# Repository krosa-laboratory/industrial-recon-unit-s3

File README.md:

# Tactical Cyber-Recon Architecture (Edge-to-C2)

A distributed, Wireless Intrusion Detection System (WIDS) and Signal Intelligence (SIGINT) platform. 

This project separates data acquisition from analysis. It utilizes an ESP32-S3 as a headless, RF edge sensor that streams raw 802.11 and BLE frames via high-speed telemetry to a Python-based Command & Control station for real-time processing, OSINT enrichment, and visualization.

## The Edge Node (Headless ESP32-S3)
A bare-metal, RTOS-driven sensor optimized for maximum radio duty-cycle and zero GUI overhead.

* **MCU:** ESP32-S3-WROOM-1 (Dual-Core Xtensa LX7)
* **Firmware:** PlatformIO / FreeRTOS (C++)
* **Architecture:**
  * **Core 0 (RF Engine):** Dedicated to hardware-level interrupts, 802.11 Promiscuous mode, CSI (Channel State Information) extraction, and passive BLE scanning.
  * **Core 1 (Telemetry Link):** Dedicated to consuming RTOS queues, serializing data into lightweight JSON, and streaming via UART at 921600 baud without blocking the radio.

## The Command & Control Station (Python GUI)
A desktop application for data ingestion, decoding, and tactical analysis.

* **Tech Stack:** Python 3, PyQt6 (UI/UX), PyQtGraph (Real-time data viz), PySerial (Async ingestion).
* **Key Capabilities:**
  * **OSINT Tracker:** Cross-references captured MAC addresses with local OUI databases to identify device manufacturers and track historical Wi-Fi probe requests.
  * **WIDS Dashboard:** Real-time detection of Deauthentication bursts, Rogue APs, and BLE saturation attacks.
  * **CSI Radar:** Generates live waterfall plots from 802.11 subcarrier perturbations to detect physical presence via microwave reflections.
  * **BLE Ecosystem Sniffer:** Parses raw Bluetooth Low Energy payloads to track corporate/IoT devices and exposes unencrypted GATT profiles.

## 🛠️ Development Philosophy & Post-Mortem
*Note: This architecture is a evolution from an initial monolithic design. By pivoting to a headless, distributed model, the system bypasses the processing and memory constraints of local displays (LVGL) and transceivers. This shift dedicates 100% of the ESP32’s compute power and RAM to raw RF acquisition, while offloading heavy OSINT and data visualization workloads to the Command & Control station.*

## ⚠️ Disclaimer
This tool is strictly for educational research, Functional Safety (FuSa) testing, and authorized auditing of Industrial Control Systems (ICS) and corporate networks.

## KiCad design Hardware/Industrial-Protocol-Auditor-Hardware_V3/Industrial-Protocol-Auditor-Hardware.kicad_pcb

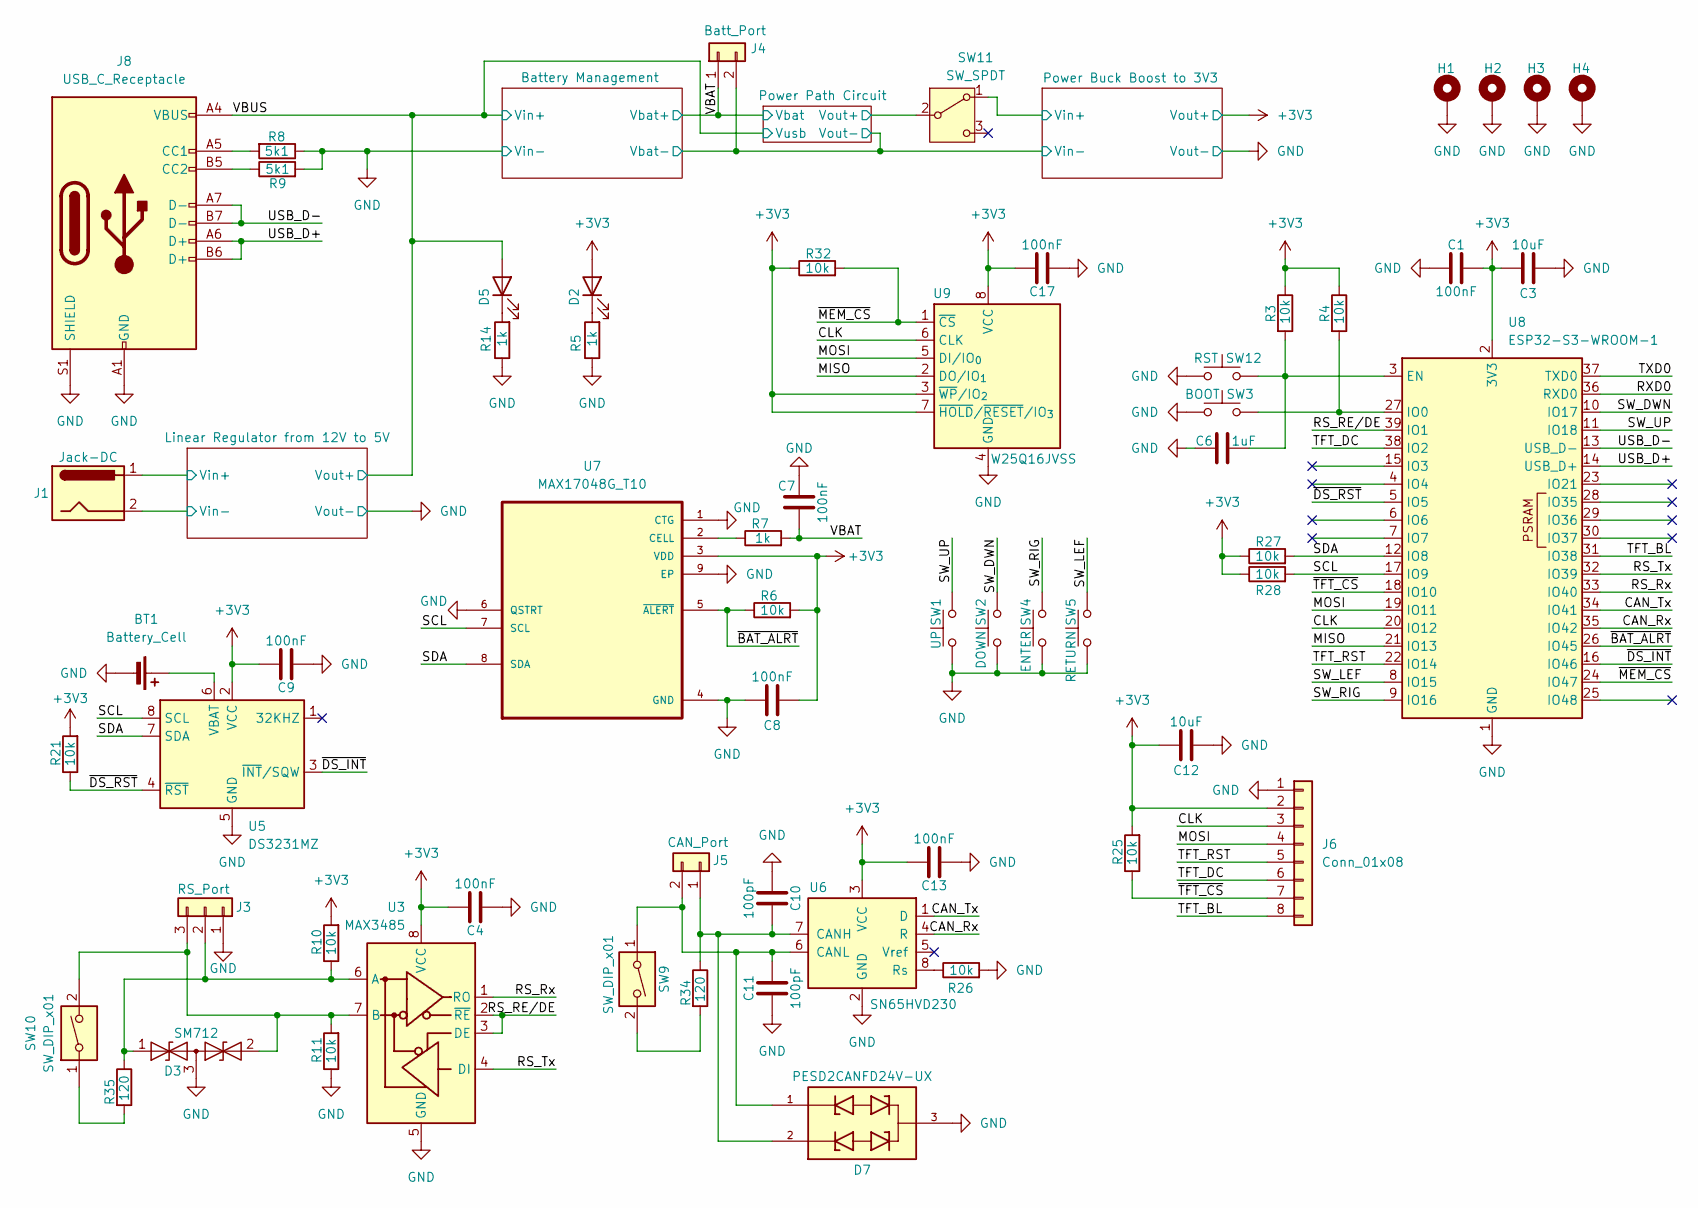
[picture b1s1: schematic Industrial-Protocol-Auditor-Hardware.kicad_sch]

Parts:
BT1: Battery_Cell; BatteryHolder_LINX_BAT-HLD-012-SMT; LCSC Part C964817
C1, C4, C7, C8, C9, C13, C17: 100nF; C_0603_1608Metric; LCSC Part C14663
C3, C12: 10uF; C_0603_1608Metric; LCSC Part C19702
C6: 1uF; C_0603_1608Metric; LCSC Part C15849
C10, C11: 100pF; C_0603_1608Metric; LCSC Part C14858
D2, D5: LED; LED_0603_1608Metric; LCSC Part C2286
D3: SM712; SOT-23; LCSC Part C7420375
D7: PESD2CANFD24V-UX; SOT-23; PARTREV V.4; LCSC Part C2687131
H1, H2, H3, H4: MountingHole_Pad; MountingHole_2.7mm_M2.5
J1: Jack-DC; BarrelJack_Horizontal; LCSC Part C16214
J3: RS_Port; TerminalBlock_MaiXu_MX126-5.0-03P_1x03_P5.00mm; LCSC Part C474882
J4: Batt_Port; JST_XH_S2B-XH-A_1x02_P2.50mm_Horizontal; LCSC Part C157931
J5: CAN_Port; TerminalBlock_MaiXu_MX126-5.0-02P_1x02_P5.00mm; LCSC Part C474881
J6: Conn_01x08; PinHeader_1x08_P2.54mm_Vertical; LCSC Part C157914
J8: USB_C_Receptacle; USB_C_Receptacle_GCT_USB4105-xx-A_16P_TopMnt_Horizontal; LCSC Part C393939
R3, R4, R6, R10, R11, R21, R25, R26, R27, R28, R32: 10k; R_0603_1608Metric; LCSC Part C25804
R5, R7, R14: 1k; R_0603_1608Metric; LCSC Part C21190
R8, R9: 5k1; R_0603_1608Metric; LCSC Part C23186
R34, R35: 120; R_0603_1608Metric; LCSC Part C22787
SW1: UP; SW_SPST_PTS645Sx43SMTR92; LCSC Part C19191552
SW2: DOWN; SW_SPST_PTS645Sx43SMTR92; LCSC Part C19191552
SW3: BOOT; SW_SPST_PTS645Sx43SMTR92; LCSC Part C19191552
SW4: ENTER; SW_SPST_PTS645Sx43SMTR92; LCSC Part C19191552
SW5: RETURN; SW_SPST_PTS645Sx43SMTR92; LCSC Part C19191552
SW9, SW10: SW_DIP_x01; SW_DIP_SPSTx01_Slide_6.7x4.1mm_W6.73mm_P2.54mm_LowProfile_J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
SW11: SW_SPDT; SS-12D11
SW12: RST; SW_SPST_PTS645Sx43SMTR92; LCSC Part C19191552
U3: MAX3485; SOIC-8_3.9x4.9mm_P1.27mm; LCSC Part C9943
U5: DS3231MZ; SOIC-8_5.3x5.3mm_P1.27mm; LCSC Part C107410
U6: SN65HVD230; SOIC-8_3.9x4.9mm_P1.27mm; LCSC Part C12084
U7: MAX17048G_T10; DFN-8-1EP_2x2mm_P0.5mm_EP0.8x1.6mm; LCSC Part C2682616
U8: ESP32-S3-WROOM-1; LCSC Part C2913202
U9: W25Q16JVSS; SOIC-8_5.3x5.3mm_P1.27mm; LCSC Part C82317

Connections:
+3V3: C1.2, C3.2, C4.2, C8.1, C9.2, C12.2, C13.2, C17.2, D2.2 (A), J6.2, R3.1, R4.1, R6.2, R10.2, R21.2, R25.2, R27.1, R28.1, R32.1, U3.8 (VCC), U5.2 (VCC), U6.3 (VCC), U7.3 (VDD), U8.2 (3V3), U9.3 (~WP/IO_{2}), U9.7 (~HOLD/~RESET/IO_{3}), U9.8 (VCC); also elsewhere on the board
/CAN_Rx: U6.4 (R), U8.35 (IO42)
/CAN_Tx: U6.1 (D), U8.34 (IO41)
/CLK: J6.3, U8.20 (IO12), U9.6 (CLK)
/Linear Regulator from 12V to 5V/Vin+: J1.1; also elsewhere on the board
/MISO: U8.21 (IO13), U9.2 (DO/IO_{1})
/MOSI: J6.4, U8.19 (IO11), U9.5 (DI/IO_{0})
/Power Buck Boost to 3V3/Vin+: SW11.1 (A); also elsewhere on the board
/Power Path Circuit/Vout+: SW11.2 (B); also elsewhere on the board
/RS_RE/DE: U3.2 (~RE), U3.3 (DE), U8.39 (IO1)
/RS_Rx: U3.1 (RO), U8.33 (IO40)
/RS_Tx: U3.4 (DI), U8.32 (IO39)
/RXD0: U8.36 (RXD0)
/SCL: R28.2, U5.8 (SCL), U7.7 (SCL), U8.17 (IO9)
/SDA: R27.2, U5.7 (SDA), U7.8 (SDA), U8.12 (IO8)
/SW_DWN: SW2.2, U8.10 (IO17)
/SW_LEF: SW5.2, U8.8 (IO15)
/SW_RIG: SW4.2, U8.9 (IO16)
/SW_UP: SW1.2, U8.11 (IO18)
/TFT_BL: J6.8, U8.31 (IO38)
/TFT_DC: J6.6, U8.38 (IO2)
/TFT_RST: J6.5, U8.22 (IO14)
/TXD0: U8.37 (TXD0)
/USB_D+: J8.A6 (D+), J8.B6 (D+), U8.14 (USB_D+)
/USB_D-: J8.A7 (D-), J8.B7 (D-), U8.13 (USB_D-)
/VBAT: C7.1, J4.1, R7.2; also elsewhere on the board
/VBUS: D5.2 (A), J8.A4 (VBUS), J8.A9 (VBUS), J8.B4 (VBUS), J8.B9 (VBUS); also elsewhere on the board
/~BAT_ALRT: R6.1, U7.5 (~ALERT), U8.26 (IO45)
/~DS_INT: U5.3 (~INT/SQW), U8.16 (IO46)
/~DS_RST: R21.1, U5.4 (~RST), U8.5 (IO5)
/~MEM_CS: R32.2, U8.24 (IO47), U9.1 (~CS)
/~TFT_CS: J6.7, R25.1, U8.18 (IO10)
GND: BT1.2 (-), C1.1, C3.1, C4.1, C6.1, C7.2, C8.2, C9.1, C10.1, C11.1, C12.1, C13.1, C17.1, D3.3 (common), D7.3, H1.1, H2.1, H3.1, H4.1, J1.2, J3.1, J4.2, J6.1, J8.A1 (GND), J8.A12 (GND), J8.B1 (GND), J8.B12 (GND), J8.S1 (SHIELD), R5.1, R8.1, R9.2, R11.1, R14.1, R26.2, SW1.1, SW2.1, SW3.1, SW4.1, SW5.1, SW12.1, U3.5 (GND), U5.5 (GND), U6.2 (GND), U7.1 (CTG), U7.4 (GND), U7.6 (QSTRT), U7.9 (EP), U8.1 (GND), U8.40 (GND), U8.41 (GND), U9.4 (GND); also elsewhere on the board
unnamed: BT1.1 (+), U5.6 (VBAT)
unnamed: D2.1 (K), R5.2
unnamed: D3.1 (A1), J3.2, R10.1, R35.1, U3.6 (A)
unnamed: D3.2 (A2), J3.3, R11.2, SW10.2, U3.7 (B)
unnamed: D5.1 (K), R14.2
unnamed: C10.2, D7.2, J5.1, R34.1, U6.7 (CANH)
unnamed: C11.2, D7.1, J5.2, SW9.1, U6.6 (CANL)
unnamed: J8.A5 (CC1), R8.2
unnamed: J8.B5 (CC2), R9.1
unnamed: R34.2, SW9.2
unnamed: R35.2, SW10.1
unnamed: R26.1, U6.8 (Rs)
unnamed: R7.1, U7.2 (CELL)
unnamed: C6.2, R3.2, SW12.2, U8.3 (EN)
unnamed: R4.2, SW3.2, U8.27 (IO0)

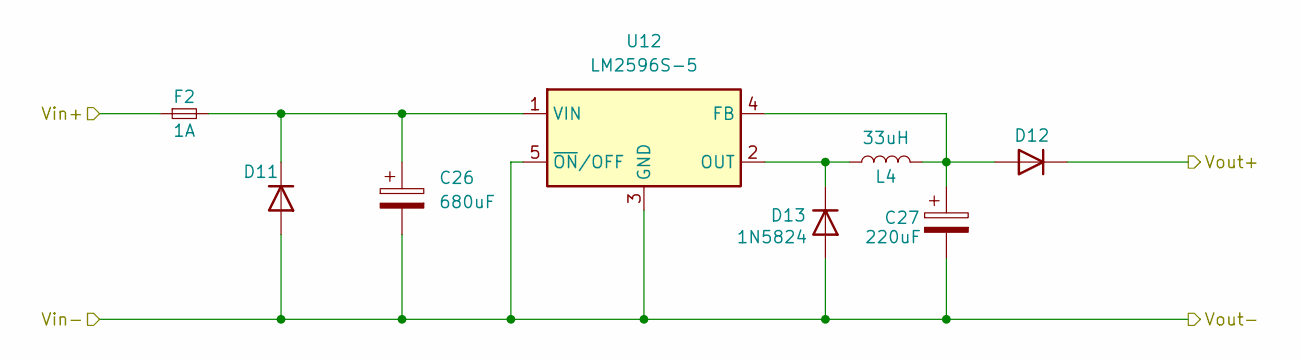
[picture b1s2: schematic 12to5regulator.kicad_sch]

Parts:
C26: 680uF; CP_Elec_10x12.5; LCSC Part C2983320
C27: 220uF; CP_Elec_6.3x7.7; LCSC Part C2887273
D11, D12, D13: 1N5824; D_SMA; LCSC Part C8678
F2: 1A; Fuse_1206_3216Metric; LCSC Part C720075
L4: 33uH; L_Sunlord_MWSA1005S; LCSC Part C6364680
U12: LM2596S-5; TO-263-5_TabPin3; LCSC Part C347421

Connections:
/Linear Regulator from 12V to 5V/Vin+: F2.1; also elsewhere on the board
/VBUS: D12.1 (K); also elsewhere on the board
GND: C26.2, C27.2, D11.2 (A), D13.2 (A), U12.3 (GND), U12.5 (~ON/OFF); also elsewhere on the board
unnamed: C26.1, D11.1 (K), F2.2, U12.1 (VIN)
unnamed: C27.1, D12.2 (A), L4.2, U12.4 (FB)
unnamed: D13.1 (K), L4.1, U12.2 (OUT)

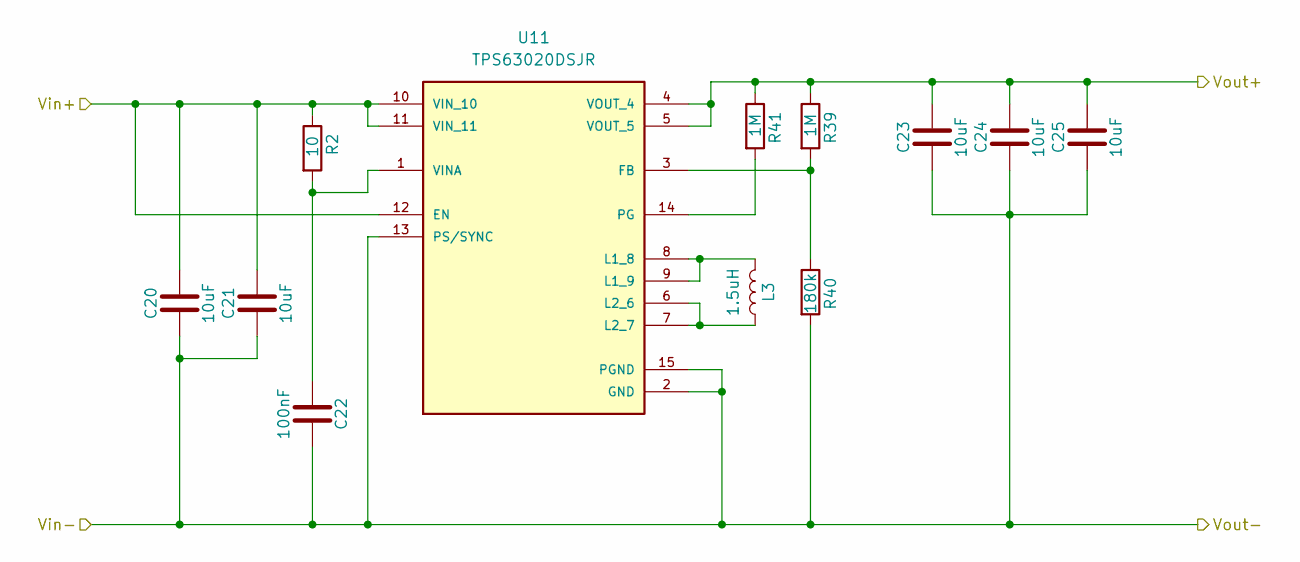
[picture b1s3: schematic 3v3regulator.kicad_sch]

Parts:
C20, C21, C23, C24, C25: 10uF; C_0603_1608Metric; LCSC Part C19702
C22: 100nF; C_0603_1608Metric; LCSC Part C14663
L3: 1.5uH; L_Chilisin_BMRx00060630; LCSC Part C5189745
R2: 10; R_0603_1608Metric; LCSC Part C22859
R39, R41: 1M; R_0603_1608Metric; LCSC Part C22935
R40: 180k; R_0603_1608Metric; LCSC Part C2906999
U11: TPS63020DSJR; IC_TPS63020DSJR; LCSC Part C15483

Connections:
+3V3: C23.2, C24.2, C25.2, R39.1, R41.1, U11.4 (VOUT_4), U11.5 (VOUT_5); also elsewhere on the board
/Power Buck Boost to 3V3/Vin+: C20.2, C21.2, R2.1, U11.10 (VIN_10), U11.11 (VIN_11), U11.12 (EN); also elsewhere on the board
GND: C20.1, C21.1, C22.2, C23.1, C24.1, C25.1, R40.2, U11.2 (GND), U11.13 (PS/SYNC), U11.15 (PGND); also elsewhere on the board
unnamed: R39.2, R40.1, U11.3 (FB)
unnamed: L3.2, U11.8 (L1_8), U11.9 (L1_9)
unnamed: L3.1, U11.6 (L2_6), U11.7 (L2_7)
unnamed: R41.2, U11.14 (PG)
unnamed: C22.1, R2.2, U11.1 (VINA)

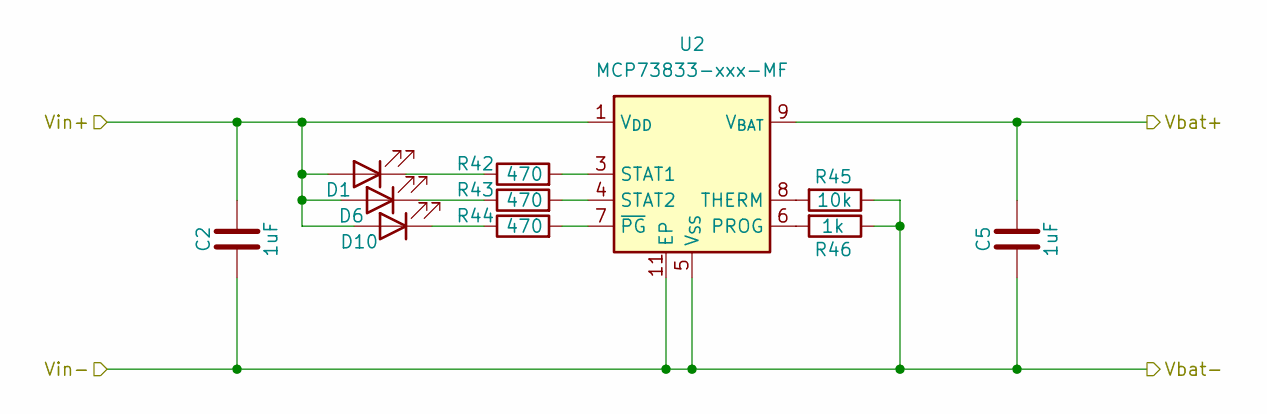
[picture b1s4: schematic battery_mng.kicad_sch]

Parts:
C2, C5: 1uF; C_0603_1608Metric; LCSC Part C15849
D1, D6, D10: LED; LED_0603_1608Metric; LCSC Part C2286
R42, R43, R44: 470; R_0603_1608Metric; LCSC Part C23179
R45: 10k; R_0603_1608Metric; LCSC Part C25804
R46: 1k; R_0603_1608Metric; LCSC Part C21190
U2: MCP73833-xxx-MF; DFN-10-1EP_3x3mm_P0.5mm_EP1.58x2.35mm; LCSC Part C340160

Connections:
/VBAT: C5.2, U2.9 (V_{BAT}), U2.10 (V_{BAT}); also elsewhere on the board
/VBUS: C2.2, D1.2 (A), D6.2 (A), D10.2 (A), U2.1 (V_{DD}), U2.2 (V_{DD}); also elsewhere on the board
GND: C2.1, C5.1, R45.1, R46.1, U2.5 (V_{SS}), U2.11 (EP); also elsewhere on the board
unnamed: D1.1 (K), R42.1
unnamed: D6.1 (K), R43.1
unnamed: D10.1 (K), R44.1
unnamed: R46.2, U2.6 (PROG)
unnamed: R42.2, U2.3 (STAT1)
unnamed: R43.2, U2.4 (STAT2)
unnamed: R45.2, U2.8 (THERM)
unnamed: R44.2, U2.7 (~PG)

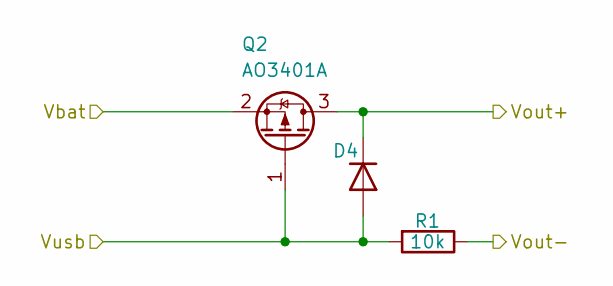
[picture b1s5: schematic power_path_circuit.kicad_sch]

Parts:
D4: 1N5824; D_SMA; LCSC Part C8678
Q2: AO3401A; SOT-23; LCSC Part C15127
R1: 10k; R_0603_1608Metric; LCSC Part C25804

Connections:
/Power Path Circuit/Vout+: D4.1 (K), Q2.3 (D); also elsewhere on the board
/VBAT: Q2.2 (S); also elsewhere on the board
/VBUS: D4.2 (A), Q2.1 (G), R1.2; also elsewhere on the board
GND: R1.1; also elsewhere on the board

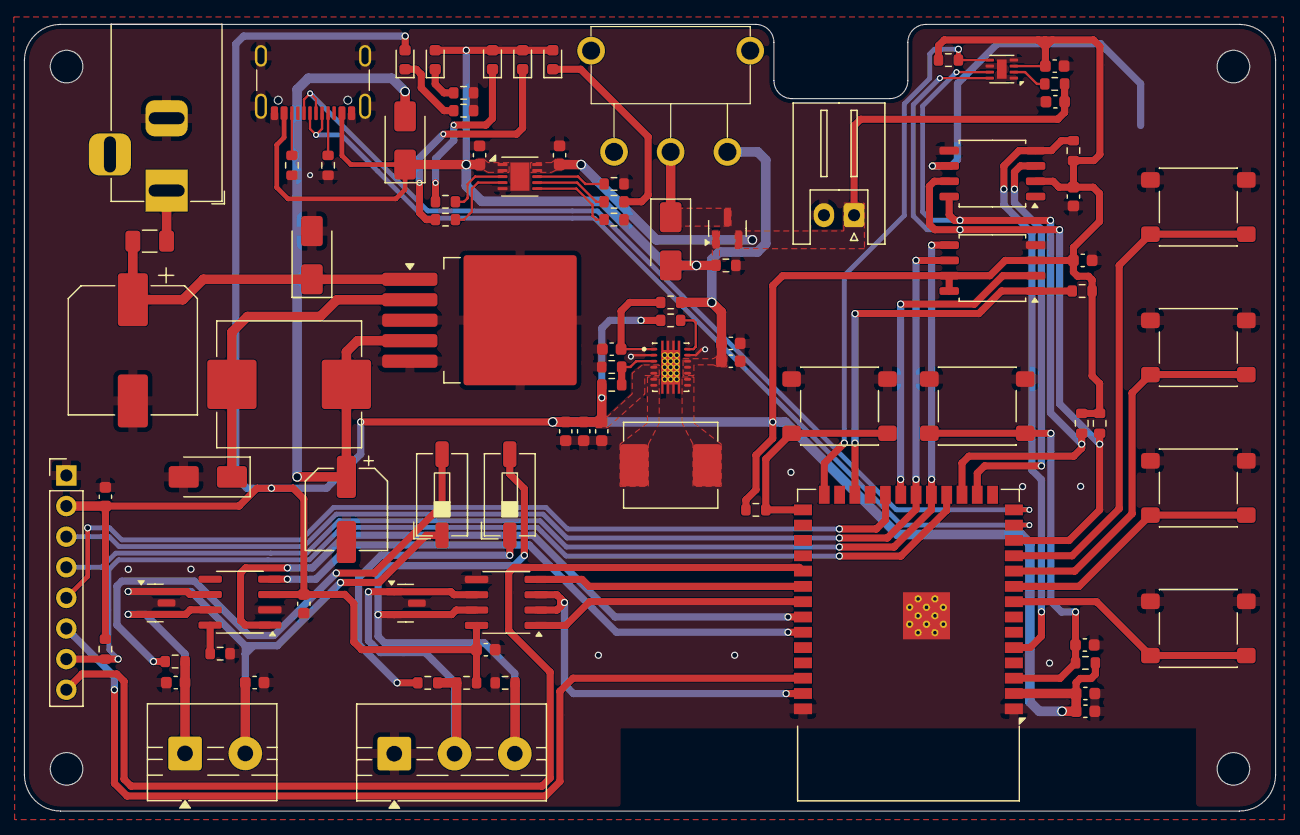
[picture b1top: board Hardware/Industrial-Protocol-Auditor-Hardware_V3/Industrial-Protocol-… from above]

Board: 2 copper layers, 103.8 x 65.3 mm, 94 parts (1 on the bottom side), 62 nets.

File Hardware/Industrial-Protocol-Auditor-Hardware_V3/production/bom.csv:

Designator,Footprint,Quantity,Value,LCSC Part #
BT1,BatteryHolder_LINX_BAT-HLD-012-SMT,1,Battery_Cell,C964817
"C1, C13, C17, C22, C4, C7, C8, C9",0603,8,100nF,C14663
"C10, C11",0603,2,100pF,C14858
"C12, C20, C21, C23, C24, C25, C3",0603,7,10uF,C19702
"C2, C5, C6",0603,3,1uF,C15849
C26,CP_Elec_10x12.5,1,680uF,C2983320
C27,CP_Elec_6.3x7.7,1,220uF,C2887273
"D1, D10, D2, D5, D6",0603,5,LED,C2286
"D11, D12, D13, D4",D_SMA,4,1N5824,C8678
D3,SOT-23,1,SM712,C7420375
D7,SOT-23,1,PESD2CANFD24V-UX,C2687131
F2,1206,1,1A,C720075
J1,BarrelJack_Horizontal,1,Jack-DC,C16214
J3,TerminalBlock_MaiXu_MX126-5.0-03P_1x03_P5.00mm,1,RS_Port,C474882
J4,JST_XH_S2B-XH-A_1x02_P2.50mm_Horizontal,1,Batt_Port,C157931
J5,TerminalBlock_MaiXu_MX126-5.0-02P_1x02_P5.00mm,1,CAN_Port,C474881
J6,PinHeader_1x08_P2.54mm_Vertical,1,Conn_01x08,C157914
J8,USB_C_Receptacle_GCT_USB4105-xx-A_16P_TopMnt_Horizontal,1,USB_C_Receptacle,C393939
L3,L_Chilisin_BMRx00060630,1,1.5uH,C5189745
L4,L_Sunlord_MWSA1005S,1,33uH,C6364680
Q2,SOT-23,1,AO3401A,C15127
"R1, R10, R11, R21, R25, R26, R27, R28, R3, R32, R4, R45, R6",0603,13,10k,C25804
"R14, R46, R5, R7",0603,4,1k,C21190
R2,0603,1,10,C22859
"R34, R35",0603,2,120,C22787
"R39, R41",0603,2,1M,C22935
R40,0603,1,180k,C2906999
"R42, R43, R44",0603,3,470,C23179
"R8, R9",0603,2,5k1,C23186
SW1,SW_SPST_PTS645Sx43SMTR92,1,UP,C19191552
"SW10, SW9",SW_DIP_SPSTx01_Slide_6.7x4.1mm_W6.73mm_P2.54mm_LowProfile_JPin,2,SW_DIP_x01,
SW11,SS-12D11,1,SW_SPDT,
SW12,SW_SPST_PTS645Sx43SMTR92,1,RST,C19191552
SW2,SW_SPST_PTS645Sx43SMTR92,1,DOWN,C19191552
SW3,SW_SPST_PTS645Sx43SMTR92,1,BOOT,C19191552
SW4,SW_SPST_PTS645Sx43SMTR92,1,ENTER,C19191552
SW5,SW_SPST_PTS645Sx43SMTR92,1,RETURN,C19191552
U11,IC_TPS63020DSJR,1,TPS63020DSJR,C15483
U12,TO-263-5_TabPin3,1,LM2596S-5,C347421
U2,DFN-10-1EP_3x3mm_P0.5mm_EP1.58x2.35mm,1,MCP73833-xxx-MF,C340160
U3,SOIC-8_3.9x4.9mm_P1.27mm,1,MAX3485,C9943
U5,SOIC-8_5.3x5.3mm_P1.27mm,1,DS3231MZ,C107410
U6,SOIC-8_3.9x4.9mm_P1.27mm,1,SN65HVD230,C12084
U7,DFN-8-1EP_2x2mm_P0.5mm_EP0.8x1.6mm,1,MAX17048G_T10,C2682616
U8,ESP32-S3-WROOM-1,1,ESP32-S3-WROOM-1,C2913202
U9,SOIC-8_5.3x5.3mm_P1.27mm,1,W25Q16JVSS,C82317

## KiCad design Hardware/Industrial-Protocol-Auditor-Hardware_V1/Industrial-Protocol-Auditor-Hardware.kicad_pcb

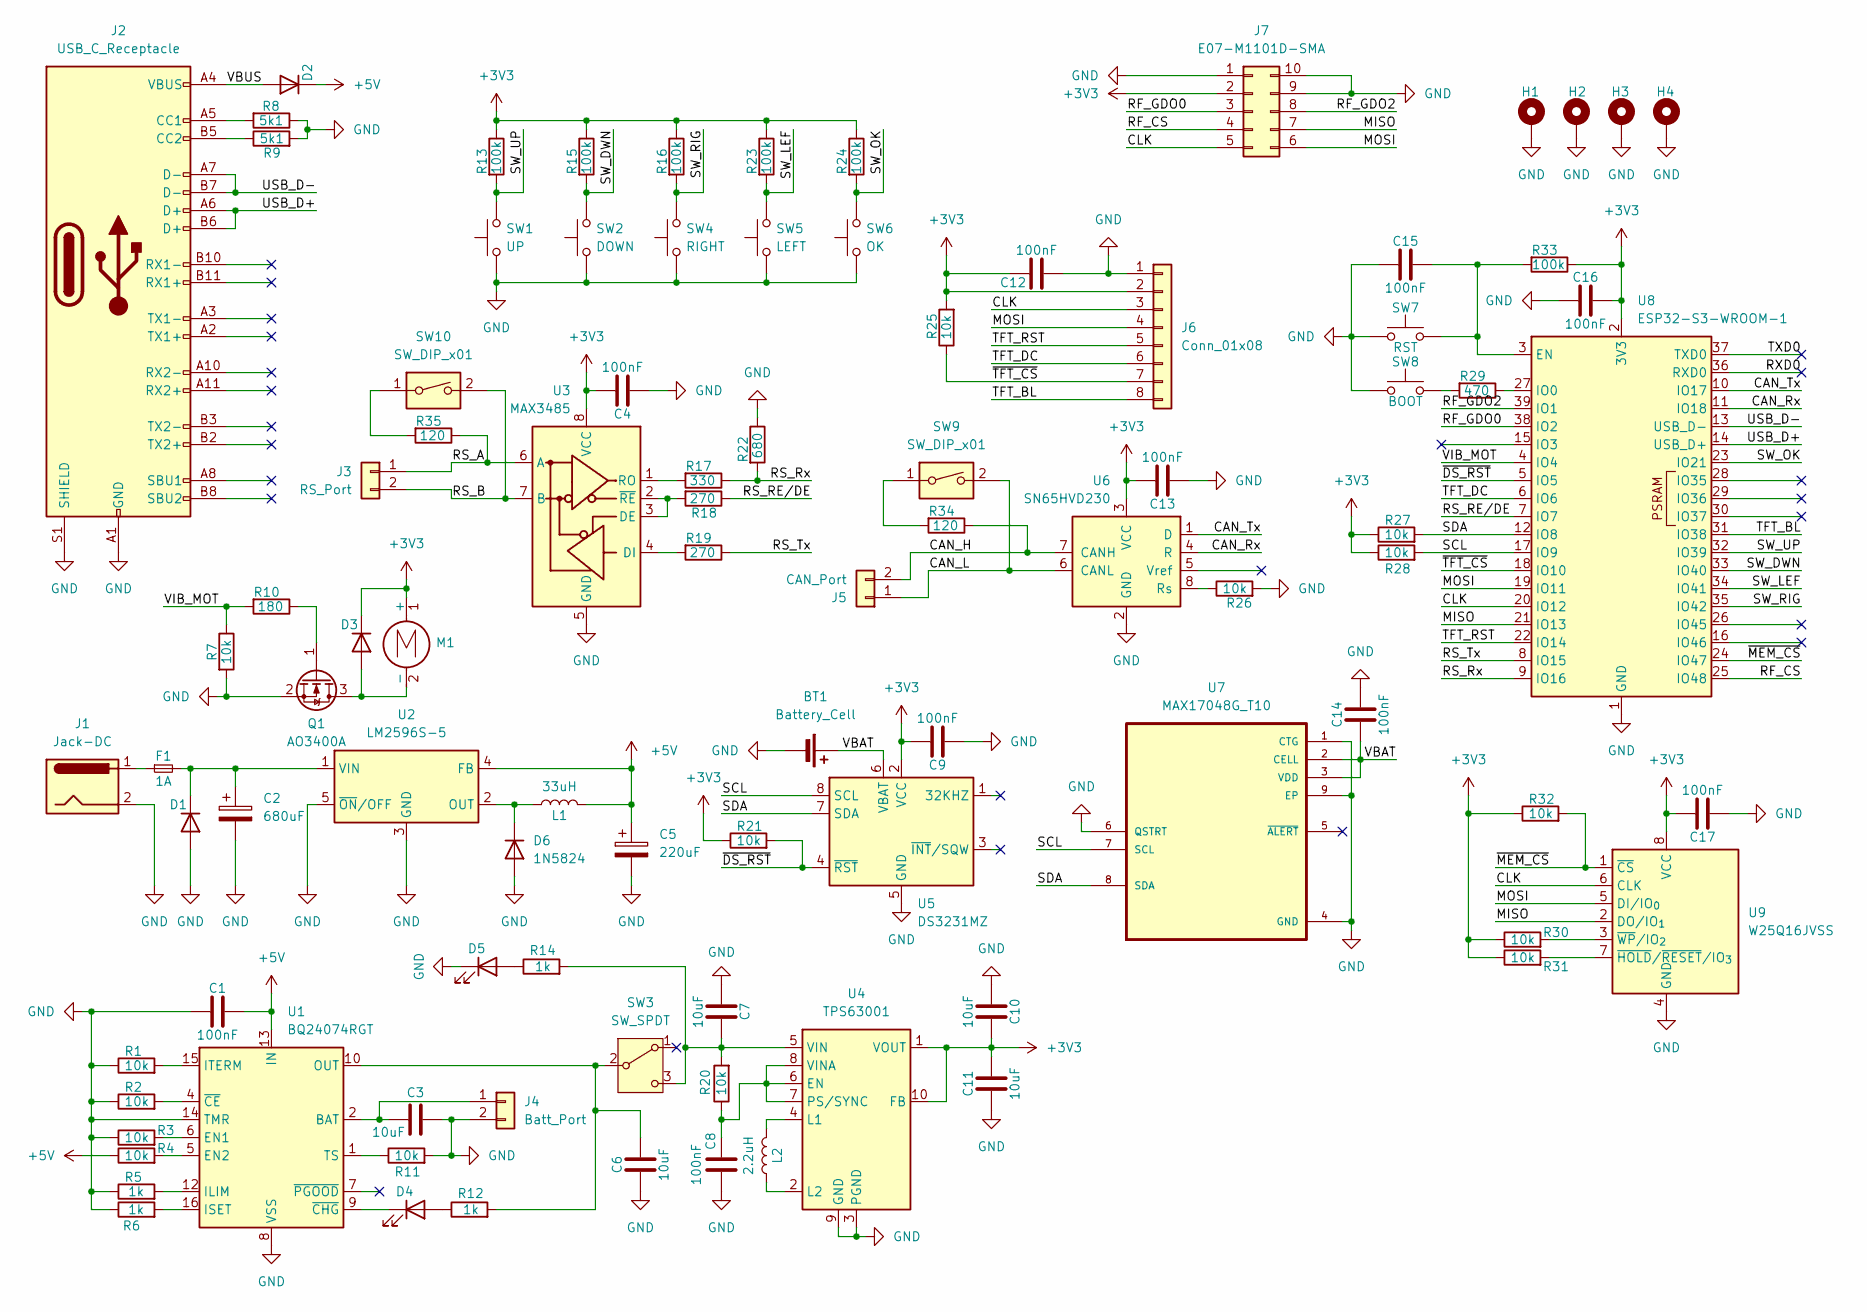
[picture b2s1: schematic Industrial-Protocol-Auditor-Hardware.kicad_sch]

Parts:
BT1: Battery_Cell; BatteryHolder_LINX_BAT-HLD-012-SMT; LCSC Part C964817
C1, C4, C8, C9, C12, C13, C14, C15, C16, C17: 100nF; C_0603_1608Metric; LCSC Part C14663
C2: 680uF; CP_Elec_10x12.5; LCSC Part C2983320
C3, C6, C7, C10, C11: 10uF; C_0603_1608Metric; LCSC Part C19702
C5: 220uF; CP_Elec_6.3x7.7; LCSC Part C2887273
D1, D2, D3, D6: 1N5824; D_SMA; LCSC Part C8678
D4, D5: LED; LED_0603_1608Metric; LCSC Part C2286
F1: 1A; Fuse_1206_3216Metric; LCSC Part C720075
H1, H2, H3, H4: MountingHole_Pad; MountingHole_2.7mm_M2.5
J1: Jack-DC; BarrelJack_Horizontal; LCSC Part C16214
J2: USB_C_Receptacle; USB_C_Receptacle_GCT_USB4105-xx-A_16P_TopMnt_Horizontal; LCSC Part C393939
J3: RS_Port; TerminalBlock_MaiXu_MX126-5.0-02P_1x02_P5.00mm; LCSC Part C474881
J4: Batt_Port; JST_XH_S2B-XH-A_1x02_P2.50mm_Horizontal; LCSC Part C157931
J5: CAN_Port; TerminalBlock_MaiXu_MX126-5.0-02P_1x02_P5.00mm; LCSC Part C474881
J6: Conn_01x08; JST_XH_S8B-XH-A_1x08_P2.50mm_Horizontal; LCSC Part C157914
J7: E07-M1101D-SMA; PinHeader_2x05_P2.54mm_Vertical
L1: 33uH; L_Coilcraft_XAL7020-102; LCSC Part C6364680
L2: 2.2uH; L_Coilcraft_XAL7020-102; LCSC Part C86092
M1: Motor_DC; PinHeader_1x02_P2.54mm_Vertical
Q1: AO3400A; SOT-23; LCSC Part C20917
R1, R2, R3, R4, R7, R11, R20, R21, R25, R26, R27, R28, R30, R31, R32: 10k; R_0603_1608Metric; LCSC Part C25804
R5, R6, R12, R14: 1k; R_0603_1608Metric; LCSC Part C21190
R8, R9: 5k1; R_0603_1608Metric; LCSC Part C23186
R10: 180; R_0603_1608Metric; LCSC Part C2907000
R13, R15, R16, R23, R24, R33: 100k; R_0603_1608Metric; LCSC Part C25803
R17: 330; R_0603_1608Metric; LCSC Part C23138
R18, R19: 270; R_0603_1608Metric; LCSC Part C22966
R22: 680; R_0603_1608Metric; LCSC Part C23228
R29: 470; R_0603_1608Metric; LCSC Part C23179
R34, R35: 120; R_0603_1608Metric; LCSC Part C23228
SW1: UP; SW_SPST_PTS645Sx43SMTR92; LCSC Part C19191552
SW2: DOWN; SW_SPST_PTS645Sx43SMTR92; LCSC Part C19191552
SW3: SW_SPDT; SS-12D11; LCSC Part C431548
SW4: RIGHT; SW_SPST_PTS645Sx43SMTR92; LCSC Part C19191552
SW5: LEFT; SW_SPST_PTS645Sx43SMTR92; LCSC Part C19191552
SW6: OK; SW_SPST_PTS645Sx43SMTR92; LCSC Part C19191552
SW7: RST; SW_SPST_PTS645Sx43SMTR92; LCSC Part C19191552
SW8: BOOT; SW_SPST_PTS645Sx43SMTR92; LCSC Part C19191552
SW9, SW10: SW_DIP_x01; SW_DIP_SPSTx01_Slide_6.7x4.1mm_W6.73mm_P2.54mm_LowProfile_J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
U1: BQ24074RGT; VQFN-16-1EP_3x3mm_P0.5mm_EP1.6x1.6mm; LCSC Part C2861252
U2: LM2596S-5; TO-263-5_TabPin3; LCSC Part C347421
U3: MAX3485; SOIC-8_3.9x4.9mm_P1.27mm; LCSC Part C9943
U4: TPS63001; Texas_DRC0010J_ThermalVias; LCSC Part C28060
U5: DS3231MZ; SOIC-8_5.3x5.3mm_P1.27mm; LCSC Part C107410
U6: SN65HVD230; SOIC-8_3.9x4.9mm_P1.27mm; LCSC Part C12084
U7: MAX17048G_T10; DFN-8-1EP_2x2mm_P0.5mm_EP0.8x1.6mm; LCSC Part C2682616
U8: ESP32-S3-WROOM-1; LCSC Part C2913202
U9: W25Q16JVSS; SOIC-8_5.3x5.3mm_P1.27mm; LCSC Part C82317

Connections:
+3V3: C4.2, C9.2, C10.2, C11.2, C12.2, C13.2, C16.2, C17.2, D3.1 (K), J6.2, J7.2, M1.1 (+), R13.1, R15.1, R16.1, R21.1, R23.1, R24.1, R25.2, R27.1, R28.1, R30.1, R31.1, R32.1, R33.1, U3.8 (VCC), U4.1 (VOUT), U4.10 (FB), U5.2 (VCC), U6.3 (VCC), U8.2 (3V3), U9.8 (VCC)
+5V: C1.2, C5.1, D2.1 (K), L1.2, R4.1, U1.13 (IN), U2.4 (FB)
/CAN_H: J5.2, R34.1, U6.7 (CANH)
/CAN_L: J5.1, SW9.2, U6.6 (CANL)
/CAN_Rx: U6.4 (R), U8.11 (IO18)
/CAN_Tx: U6.1 (D), U8.10 (IO17)
/CLK: J6.3, J7.5, U8.20 (IO12), U9.6 (CLK)
/MISO: J7.7, U8.21 (IO13), U9.2 (DO/IO_{1})
/MOSI: J6.4, J7.6, U8.19 (IO11), U9.5 (DI/IO_{0})
/RF_CS: J7.4, U8.25 (IO48)
/RF_GDO0: J7.3, U8.38 (IO2)
/RF_GDO2: J7.8, U8.39 (IO1)
/RS_A: J3.1, R35.1, U3.6 (A)
/RS_B: J3.2, SW10.2, U3.7 (B)
/RS_RE/DE: R18.1, U8.7 (IO7)
/RS_Rx: R17.1, R22.2, U8.9 (IO16)
/RS_Tx: R19.1, U8.8 (IO15)
/RXD0: U8.36 (RXD0)
/SCL: R28.2, U5.8 (SCL), U7.7 (SCL), U8.17 (IO9)
/SDA: R27.2, U5.7 (SDA), U7.8 (SDA), U8.12 (IO8)
/SW_DWN: R15.2, SW2.2, U8.33 (IO40)
/SW_LEF: R23.2, SW5.2, U8.34 (IO41)
/SW_OK: R24.2, SW6.2, U8.23 (IO21)
/SW_RIG: R16.2, SW4.2, U8.35 (IO42)
/SW_UP: R13.2, SW1.2, U8.32 (IO39)
/TFT_BL: J6.8, U8.31 (IO38)
/TFT_DC: J6.6, U8.6 (IO6)
/TFT_RST: J6.5, U8.22 (IO14)
/TXD0: U8.37 (TXD0)
/USB_D+: J2.A6 (D+), J2.B6 (D+), U8.14 (USB_D+)
/USB_D-: J2.A7 (D-), J2.B7 (D-), U8.13 (USB_D-)
/VBAT: BT1.1 (+), C14.1, U5.6 (VBAT), U7.2 (CELL), U7.3 (VDD)
/VBUS: D2.2 (A), J2.A4 (VBUS), J2.A9 (VBUS), J2.B4 (VBUS), J2.B9 (VBUS)
/VIB_MOT: R7.1, R10.2, U8.4 (IO4)
/~DS_RST: R21.2, U5.4 (~RST), U8.5 (IO5)
/~MEM_CS: R32.2, U8.24 (IO47), U9.1 (~CS)
/~TFT_CS: J6.7, R25.1, U8.18 (IO10)
GND: BT1.2 (-), C1.1, C2.2, C3.2, C4.1, C5.2, C6.1, C7.1, C8.1, C9.1, C10.1, C11.1, C12.1, C13.1, C14.2, C15.1, C16.1, C17.1, D1.2 (A), D5.1 (K), D6.2 (A), H1.1, H2.1, H3.1, H4.1, J1.2, J2.A1 (GND), J2.A12 (GND), J2.B1 (GND), J2.B12 (GND), J2.S1 (SHIELD), J4.2, J6.1, J7.1, J7.9, J7.10, Q1.2 (S), R1.1, R2.1, R3.1, R5.1, R6.1, R7.2, R8.1, R9.2, R11.2, R22.1, R26.2, SW1.1, SW2.1, SW4.1, SW5.1, SW6.1, SW7.1, SW8.1, U1.8 (VSS), U1.14 (TMR), U1.17 (VSS), U2.3 (GND), U2.5 (~ON/OFF), U3.5 (GND), U4.3 (PGND), U4.9 (GND), U4.11 (PGND), U5.5 (GND), U6.2 (GND), U7.1 (CTG), U7.4 (GND), U7.6 (QSTRT), U7.9 (EP), U8.1 (GND), U8.40 (GND), U8.41 (GND), U9.4 (GND)
unnamed: C2.1, D1.1 (K), F1.2, U2.1 (VIN)
unnamed: D3.2 (A), M1.2 (-), Q1.3 (D)
unnamed: D4.2 (A), R12.1
unnamed: D4.1 (K), U1.9 (~CHG)
unnamed: D5.2 (A), R14.1
unnamed: D6.1 (K), L1.1, U2.2 (OUT)
unnamed: F1.1, J1.1
unnamed: J2.A5 (CC1), R8.2
unnamed: J2.B5 (CC2), R9.1
unnamed: C3.1, J4.1, U1.2 (BAT), U1.3 (BAT)
unnamed: Q1.1 (G), R10.1
unnamed: R29.2, SW8.2
unnamed: R34.2, SW9.1
unnamed: R35.2, SW10.1
unnamed: C6.2, R12.2, SW3.2 (B), U1.10 (OUT), U1.11 (OUT)
unnamed: C7.2, R14.2, R20.2, SW3.3 (C), U4.5 (VIN)
unnamed: R3.2, U1.6 (EN1)
unnamed: R4.2, U1.5 (EN2)
unnamed: R5.2, U1.12 (ILIM)
unnamed: R6.2, U1.16 (ISET)
unnamed: R1.2, U1.15 (ITERM)
unnamed: R11.1, U1.1 (TS)
unnamed: R2.2, U1.4 (~CE)
unnamed: R18.2, U3.2 (~RE), U3.3 (DE)
unnamed: R19.2, U3.4 (DI)
unnamed: R17.2, U3.1 (RO)
unnamed: C8.2, R20.1, U4.6 (EN), U4.7 (PS/SYNC), U4.8 (VINA)
unnamed: L2.2, U4.4 (L1)
unnamed: L2.1, U4.2 (L2)
unnamed: R26.1, U6.8 (Rs)
unnamed: C15.2, R33.2, SW7.2, U8.3 (EN)
unnamed: R29.1, U8.27 (IO0)
unnamed: R31.2, U9.7 (~HOLD/~RESET/IO_{3})
unnamed: R30.2, U9.3 (~WP/IO_{2})

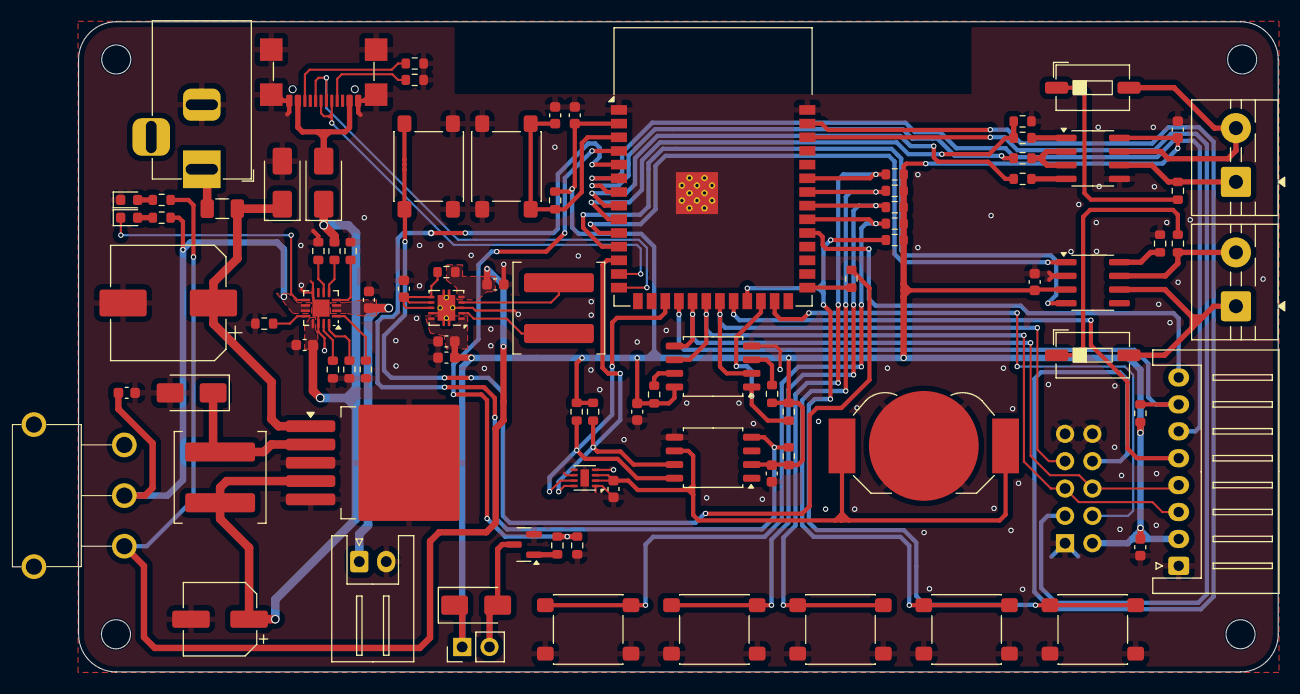
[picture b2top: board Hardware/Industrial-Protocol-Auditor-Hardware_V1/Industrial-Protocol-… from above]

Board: 2 copper layers, 111.5 x 60.4 mm, 94 parts (1 on the bottom side), 70 nets.

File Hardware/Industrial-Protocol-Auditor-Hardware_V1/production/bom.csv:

Designator,Footprint,Quantity,Value,LCSC Part #
BT1,BatteryHolder_LINX_BAT-HLD-012-SMT,1,Battery_Cell,C964817
"C1, C12, C13, C14, C15, C16, C17, C4, C8, C9",0603,10,100nF,C14663
"C10, C11, C3, C6, C7",0603,5,10uF,C19702
C2,CP_Elec_10x12.5,1,680uF,C2983320
C5,CP_Elec_6.3x7.7,1,220uF,C2887273
"D1, D2, D3, D6",D_SMA,4,1N5824,C8678
"D4, D5",0603,2,LED,C2286
F1,1206,1,1A,C720075
J1,BarrelJack_Horizontal,1,Jack-DC,C16214
J2,USB_C_Receptacle_GCT_USB4105-xx-A_16P_TopMnt_Horizontal,1,USB_C_Receptacle,C393939
J3,TerminalBlock_MaiXu_MX126-5.0-02P_1x02_P5.00mm,1,RS_Port,C474881
J4,JST_XH_S2B-XH-A_1x02_P2.50mm_Horizontal,1,Batt_Port,C157931
J5,TerminalBlock_MaiXu_MX126-5.0-02P_1x02_P5.00mm,1,CAN_Port,C474881
J6,JST_XH_S8B-XH-A_1x08_P2.50mm_Horizontal,1,Conn_01x08,C157914
J7,PinHeader_2x05_P2.54mm_Vertical,1,E07-M1101D-SMA,-
L1,L_Coilcraft_XAL7020-102,1,33uH,C6364680
L2,L_Coilcraft_XAL7020-102,1,2.2uH,C86092
M1,PinHeader_1x02_P2.54mm_Vertical,1,Motor_DC,-
Q1,SOT-23,1,AO3400A,C20917
"R1, R11, R2, R20, R21, R25, R26, R27, R28, R3, R30, R31, R32, R4, R7",0603,15,10k,C25804
R10,0603,1,180,C2907000
"R12, R14, R5, R6",0603,4,1k,C21190
"R13, R15, R16, R23, R24, R33",0603,6,100k,C25803
R17,0603,1,330,C23138
"R18, R19",0603,2,270,C22966
R22,0603,1,680,C23228
R29,0603,1,470,C23179
"R34, R35",0603,2,120,C23228
"R8, R9",0603,2,5k1,C23186
SW1,SW_SPST_PTS645Sx43SMTR92,1,UP,C19191552
"SW10, SW9",SW_DIP_SPSTx01_Slide_6.7x4.1mm_W6.73mm_P2.54mm_LowProfile_JPin,2,SW_DIP_x01,
SW2,SW_SPST_PTS645Sx43SMTR92,1,DOWN,C19191552
SW3,SS-12D11,1,SW_SPDT,C431548
SW4,SW_SPST_PTS645Sx43SMTR92,1,RIGHT,C19191552
SW5,SW_SPST_PTS645Sx43SMTR92,1,LEFT,C19191552
SW6,SW_SPST_PTS645Sx43SMTR92,1,OK,C19191552
SW7,SW_SPST_PTS645Sx43SMTR92,1,RST,C19191552
SW8,SW_SPST_PTS645Sx43SMTR92,1,BOOT,C19191552
U1,VQFN-16-1EP_3x3mm_P0.5mm_EP1.6x1.6mm,1,BQ24074RGT,C2861252
U2,TO-263-5_TabPin3,1,LM2596S-5,C347421
U3,SOIC-8_3.9x4.9mm_P1.27mm,1,MAX3485,C9943
U4,Texas_DRC0010J_ThermalVias,1,TPS63001,C28060
U5,SOIC-8_5.3x5.3mm_P1.27mm,1,DS3231MZ,C107410
U6,SOIC-8_3.9x4.9mm_P1.27mm,1,SN65HVD230,C12084
U7,DFN-8-1EP_2x2mm_P0.5mm_EP0.8x1.6mm,1,MAX17048G_T10,C2682616
U8,ESP32-S3-WROOM-1,1,ESP32-S3-WROOM-1,C2913202
U9,SOIC-8_5.3x5.3mm_P1.27mm,1,W25Q16JVSS,C82317

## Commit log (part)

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2026-01-15 Added files of hardware designs, assignments and power consumptions used for the project.
2026-01-15 Added file needed to workflow
2026-01-29 Created the ESP-IDF project wioth Vs Code extension to try ESP32-S3 microcontroller in the custom PCB for the device.
2026-01-29 Tested display functioning with custom PCB and ESP-IDF extension. All works fine by now.
2026-02-06 Removed ESP-IDF files. I'm migrating to PlatformIO + VS Code.
2026-02-06 Created PlatformIO project.
2026-02-07 Configured PlatformIO with microcontroller specifications.
2026-02-10 Prepared a test for an ESP32-WROOM-32 NodeMCU to test. Maybe I develop the prototype in breadboard and let the PCB unused because it has problems with USB comms.
2026-02-10 Created a first approach to the main menu and navigation inputs. Adjusted some params in the compilation to fit the screen perfectly.
2026-02-14 Reoranizaed the code and redone some code to implement more than one screen. Tested navigation and sub-menus.
2026-02-17 Fixed a bug that occurs entering the CAN Bus screen and cause the screen to not start automatically, needing a button activation to strat emulating readings.
2026-02-17 First attempt for the second menu, WiFi Scanner. I need to rework the menu management to add sub-menus for each option of the main menu.
2026-02-22 Restructured the screen management to add intermediate screens between main menu option and each tool.
2026-02-22 Structured again the folder structure and fixed all #include and classes to work fine the Main menu and the CAN Bus tools.
2026-02-22 Fixed Can bus tools internal private variables name and implemented the WiFi Scanner tool.
2026-02-22 Implemented the promiscuous monitor as a WiFi tool.
2026-02-22 Removed unnecessary file. In the future will be added another tool to the WiFi tool menu.
2026-03-02 Added a WIDS (Wireless Intruder Detection System) tool in the WiFi menu.
2026-03-02 Created a new tool for BLE scanning.
2026-03-02 Created a new tool named GATT scanner. Need tests.
2026-03-03 Tested GATT BLE tool and implemented a new tool for RS485 sniffing.
2026-03-03 Created a simulated ModBus Scanner tool for RS485 menu.
2026-03-03 Implemented the last menu, System options to see ESP info and reboot it manually. Now we have to work in the real implementation for CAN and RS, removing all data simulation.
2026-03-10 Created a new version of the Hardware, fixing some problems finded in the first attempt of PCB.
